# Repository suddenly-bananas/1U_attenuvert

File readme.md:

This module is an attempt to reproduce the functionality of the Intellijel Quadratt for private use (not for sale!), i.e. four independent attenuators/attenuverters, which can be mixed together through normalized mixing, although some modifications are included regarding output LEDs and jack input normalization. The schematics are fairly straightforward and consists mainly of usual inverting opamp mixing stages. Aside from having a new utility module at hand, the main goal of this project was to have a relatively simple module with which I can make my first experiences with SMD-components, SMD-assembly services and 4-layer-PCB-design.

# Picdump

front panel

finished module

assembled PCB and front-panel

layout top

layout bottom

layout power layer

schematics

# Circuit Explanation

The circuit consists of four nearly identical attenuverter cores in the following configuration: 

Each attenuverter core can be switched between attenuator (Gain ranging from 0 to 1) and attenuverter (Gain ranging from -1 to 1) modes. Each input is normalized to +5V or +10V, see the section about input normalization below. If no cable is plugged in the output of its respective channel, the output signal is automatically mixed to the next channel, see the section about output normalization in the documentation.

# [Click here for a detailed analysis of the circuit!](./docu/docu.pdf)

<!-- ## Attenuverter Core Circuit

### Inverting OPamp stages

The core circuit for each channel consists of two unity gain inverting amplifier stages, i.e. stages with a gain of -1. Quick reminder about the golden rules for opamps with negative feedback: Rule 1 states that the opamp will make it so that its two input nodes have the same potential. Rule 2 states that no current can flow into the opamp. With this in mind, the inverting amplifier works as follows:

With this we arrive at:

For having not only a fixed gain of -1 but make it adjustable, one can insert a potentiometer as follows:

In this case, the potentiometer is of course nothing else than two resistors $R_1, R_2$ with $R_{pot} = R_1+R_2$, where $R_{pot}$ is the total resistance of the pot:

As before, by using the opamp rules, this can be analyzed to arrive at a general more general formula for the gain of the circuit. First note, that because of "virtual ground" at the negative terminal of the opamp, $R_1$ and $R_2$ form a current divider as follows:

Solving for $I_1,$ we obtain
$$ I_1 = I - I_2 = I - \frac{R_1}{R_2}\cdot I_1, $$
hence
$$ I = I_1+\frac{R_1}{R_2}\cdot I_1 = (1+\frac{R_1}{R_2})\cdot I_1 $$
and thus 
$$ I_1 = \frac{I}{1+ \frac{R_1}{R_2}}. $$
Writing $R_1||R_2$ for the resistance of $R_1$ parallel to $R_2,$ the total current $I$ is given by
$$ I = \frac{U_{in}}{R_{in} + (R_1||R_2)} = \frac{U_{in}}{R_{in} + \frac{1}{\frac{1}{R_1}+\frac{1}{R_2}}}.$$
This leads to
$$\begin{align*} 
    I_1 &= I\cdot \frac{1}{1+ \frac{R_1}{R_2}} \\
    &= \frac{U_{in}}{R_{in} + \frac{1}{\frac{1}{R_1}+\frac{1}{R_2}}}\cdot \frac{1}{1+ \frac{R_1}{R_2}}\\
    &= \frac{U_{in}}{R_{in} + \frac{R_1R_2}{R_1+R_2}}\cdot \frac{R_2}{R_2+ R_1}\\
    &= \frac{U_{in}R_2}{R_{in}(R_2+R_1) + R_1R_2} \\
    &= \frac{U_{in}R_2}{R_{in}R_{pot} + R_1R_2}
\end{align*}$$
remembering that $R_{pot} = R_2 + R_1$. Again we have $U_{out} = -I_1\cdot R_F$ by inverting opamp amplifier rules and thus arrive at the general formula
$$ U_{out} = -U_{in}\cdot \frac{R_2R_F}{R_{in}R_{pot} + R_1R_2}. $$
Ideally, we would want to have a linear relationship between potentiometer position, i.e. the value of $R_2$, and gain of our circuit. But considering $R_2$ as the parameter of the gain function $f$, i.e.
$$ f(R_2) = - \frac{R_2R_F}{R_{in}R_{pot} + R_1R_2}, $$
this looks all but linear! Luckily, we can make some assumptions, because of course in reality we don't care if it is really mathematically linear or only "linear enough". If we assume for now, that $R_{in}$ is much bigger than $R_{pot},$ then since both $R_1\leq R_{pot}<<R_{in}$ and $R_2\leq R_{pot}<<R_{in},$ we can approximate
$$ R_{in}R_{pot} + R_1R_2 \approx R_{in}R_{pot}. $$
If we further say that $R_{in} = R_F$ (in practice we choose 100k for both), the gain function simplifies to 
$$ f(R_2) \approx \frac{R_2}{R_{pot}}, $$ 
which is linear! Or in other words $U_{out}\approx -U_{in}\cdot \frac{R_2}{R_{pot}}$

So, what value do we choose for $R_{pot}$? The following plots show the gain $-{U_{out}}/{U_{in}}$ of the circuit for different values of $R_{pot}$ and we can easily see that a value of 10k leads to "linear enough".

We close this section with an inverting mixer configuration. It's basically the same as before, but with multiple input voltages and corresponding resistors (Remember that no current can flow inside of the opamp):

So we see, that the output is just an inverted copy of the sum of the two input voltages, but each input scaled acoordingly by $R_1$ and $R_2$ respectively.

### Attenuator / Attenuverter Circuit

Now we come to the actual attenuverter core. Let's have a look at the attenuverter circuit for channel 1:

If the switch connects to ground as in the picture, the situation is exactly as explained before; The first opamp outputs $-U_{in}\cdot c,$ where $c$ is a value between 0 and 1, depending on the pot position (this is approximately $R_2/R_{pot}$ as in the previous section). The next opamp has a gain of $-1$, so the total output is $U_{out} = c\cdot U_{in}.$ Attenuation achieved!

Now assume the switch is in the other position, i.e. one side of the potentiometer is connected to the negative terminal of the second opamp. Since both sides of the potentiometer are connected to input terminals of opamps, they both sit at "virtual ground" aka 0V. Let's analyze some concrete potentiometer positions:

- Pot fully turned clockwise:

Both ends of the potentiometer sit at 0V, no current flows through the pot, so the first opamp outputs $-U_{in}$ and the second one inverts it again, arriving at $U_{out} = U_{in}.$
- Pot in middle position:

As before, the pot divides the current, so roughly half of the input current flow through either side of the pot. The first opamp then outputs roughly $\approx -0.5\cdot U_{in}$. This again forces a negative to current through the 100k-resistor connecting the first opamp to the second one, which then cancels with the current coming from the lower part of the pot. Total output: 0V 
- Pot fully turned counterclockwise:

Again both ends of the potentiometer sit at 0V, so all input current has to flow to the second opamp, which inverts the signal, so we arrive at $U_{out}=-U_{in}.$

For potentiometer positions in between, we interpolate the total gain of the circuit from -1 to 1, somewhat linearly by the choice of 10k for the pot which is small enough relative to the other resistors. In other words: Attenuvertion achieved!

## LED Driver Circuit

The LED driver uses an opamp-circuit that acts as a voltage to current converter:

It works as follows: No current can flow into the opamp, so $I_1 = I_2.$ Furthermore, $U_-=U_+=U_{in},$ so $I_1 = I_2 = U_-/R_2 = U_{in}/R_2.$ Hence the current through $R_1$ is completely determined by the input voltage scaled by the fixed value of $R_2.$ In particular, it depends linearly on $U_{in}!$ Note that the value of $R_1$ is completely irrelevant for this calculation. (At least in theory; in practice, the opamp must be able to supply an output voltage big enough so that $U_- = U_+.$ This works as long as the opamp is not in saturation territory.) Thus, we can easily swap $R_1$ with an LED:

And as such, we have an LED driver where the current through the LED depends linearly on $U_{in}$ and is scaled by the fixed series resistor $R_2.$ Note however, that this works only for positive input voltages, because for a negative input voltage, also $I_2$ and thus $I_1$ would be negative, but this is prevented by orientation of the LED.

In our circuit, we have two LEDs: A yellow one for positive voltages, and a blue one for negative voltages:

While in theory, one could use on opamp for both LEDs by wiring the LEDs in an antiparallel way in the negative feedback loop, our approach has the upside that the series resistor can be chosen individually for each LED. With the LEDs I have (Standard 3mm LEDs from [banzaimusic.com](banzaimusic.com)), if I use the same series resistor for both LEDs, either the yellow one is barely visible or the blue one kills my eyesight. Through testing on breadboard, I arrived at 470 Ohms for the yellow LED and 47 kOhms for the blue LED.

One last note: When using opamps in such a way that the terminals do not sit at 0V, i.e. (virtual) ground, there is an effect called [phase reversal](https://northcoastsynthesis.com/news/whats-the-deal-with-phase-reversal/). In order to prevent this, we scale the voltage goging to the LED drivers by 1/2, using a simple voltage divider. Since the previous stage can output at most +/-12V, this limits the input of the LED-drivers to +/-6V which is a safe range. Of course, this has to be taken into account when choosing appropriate LED series resistors.

## Output Normalization Mixing

As in the Intellijel Quadratt, I wanted to implement mixing through normalization, i.e. if no cable is plugged into the output jack of some channel, the output signal shall automatically be mixed to the output of the next stage. "Simple!" I thought, naive as I am. "I just add the output of one channel through a 100k-resistor to the first opamp-stage of the next channel." (At this point, you have to recall the basic mixing circuit at the end of the section about inverting opamp stages.) Let's see what happens.

First assume the switch of the next channel is in attenuation mode:

Let $U_{prev}$ be the signal from the previous channel and $V_{in}$ be the input signal of the next channel, which is seen by the first opamp after scaling it with the potentiometer. If the sum of both signals $V_{in}+U_{prev}$ is inside the range of +/-12V, everything works as expected as the first opamp stage outputs $-(V_{in}+U_{prev}),$ which by the second opamp stage gets inverted again to arrive at $V_{in}+U_{prev}$ on the output.

If $V_{in}+U_{prev}$ exceeds the range of +/-12V, then the first opamp saturates. In this case this is no problem, since the excess current at the input can just flow through the pot to ground. So the voltage is just clamped at +/-12V in this case, which is also how the circuit is expected to work.

Now assume we are in attenuvertion mode:

With the notation as above, if $V_{in}+U_{prev}$ does not exceed +/-12V, everything works as before, the only difference being that the input voltage $U_{in}$ is processed by both opamp stages as explained in the previous section about the attenuverter circuit.

If the first opamp goes into saturation, however, there are some drastic effects. Assume that $U_{prev}=12V,$ so this signal alone is enough to saturate the opamp so that its output sits at -12V. Also assume that the pot is fully clockwise, so it can be regarded as a resistance of 10k from the negative terminal of the first opamp to the negative terminal of the second opamp. The current $I_1$ through $R_1$ can now not flow through $R_F,$ since the first opamp is already in saturation and thus cannot go any lower than -12V, which would be necessary to sink more current. Hence, $I_1$ must flow through the pot directly to the second opamp. Suppose we have $U_{in}=5V,$ hence $I_1=5V/100k\Omega = 50\mu A.$ In theory, we would want to have the sum $U_{in}+U_{prev}=17V,$ which gets clamped to 12V, at the total output. But what actually happens is, that the second opamp sees $-12V/100k + 50\mu A = -70\mu A$ at its negative input, hence it outputs 7V, to have a current of $7V/100k\Omega = 70\mu A$ flowing from its output through the feedback resistor to its negative terminal. So, actually $U_{in}$ got subtracted from $U_{prev},$ totally not wat we aimed for!

To overcome this problem we changed the feedback resistor of the first opamp stage from 100k to 51k, effectively halving the voltage gain of this stage. This prevents the opamp from ever going into saturation mode if both $U_{prev}$ and $U_{in}$ stay inside a +/-12V-range. Then the resistor going from the first opamp to the second one also has to be changed to 51k, which has the effect that the second opamp has a gain of -2 for the voltage coming out of the first opamp, which reverses the gain halving we did before. 

Note that this is of course not necessary for the first channel, as there is normalization mixing in this case. In practice, this approach has the downside that inherent offset voltages as well as noise from the first opamp get amplified by a factor of 2 by the second opamp. But it has to be seen if this is even noticable in practice. -->

# Changes for Next Version

- If Layout has to be changed: Swap all LEDs to the right of their respective output-jack. This should greatly simplify the PCB layout routing.
- Fix positioning of power pinheader

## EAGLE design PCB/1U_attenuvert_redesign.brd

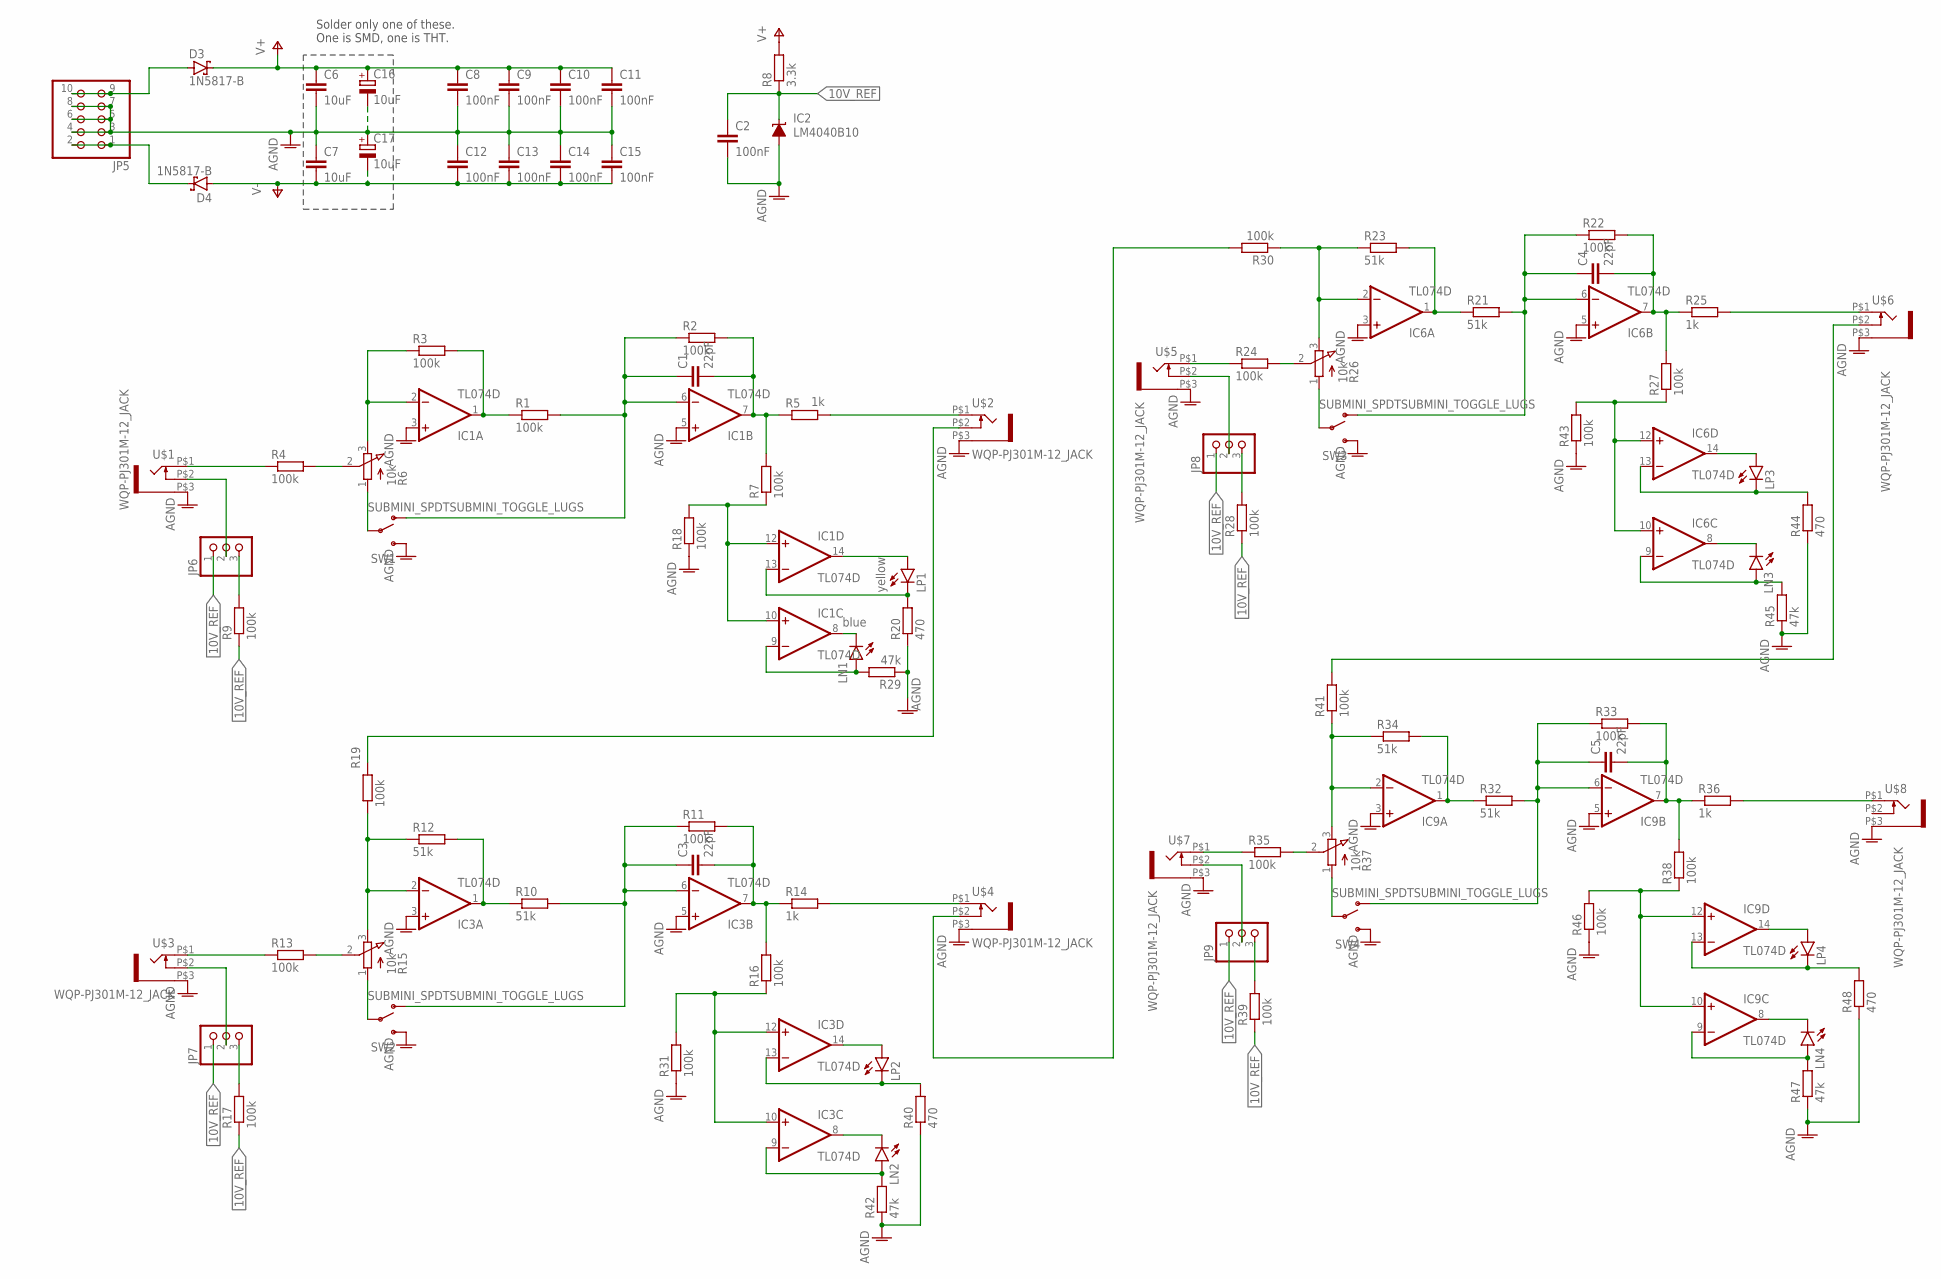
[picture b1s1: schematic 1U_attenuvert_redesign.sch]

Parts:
C1, C3, C4, C5: 22pF; C0603
C2, C8, C9, C10, C11, C12, C13, C14, C15: 100nF; C0603
C6, C7: 10uF; C0805
C16, C17: 10uF; E2,5-6
D3, D4: 1N5817-B; DO41-7.6
IC1, IC3, IC6, IC9: TL074D; SO14
IC2: LM4040B10; DBZ_R-PDSO-G3
JP5: PINHD-2X5; 2X05
JP6, JP7, JP8, JP9: PINHD-1X3; 1X03
LN1: blue; LED3MM
LN2, LN3, LN4: LED3MM
LP1: yellow; LED3MM
LP2, LP3, LP4: LED3MM
R1, R2, R3, R4, R7, R9, R11, R13, R16, R17, R18, R19, R22, R24, R27, R28, R30, R31, R33, R35, R38, R39, R41, R43, R46: 100k; R0603
R5, R14, R25, R36: 1k; R0603
R6, R15, R26, R37: 10k; EVUFXL
R8: 3.3k; R0603
R10, R12, R21, R23, R32, R34: 51k; R0603
R20, R40, R44, R48: 470; R0603
R29, R42, R45, R47: 47k; R0603
SW1, SW2, SW3, SW4: SUBMINI_SPDTSUBMINI_TOGGLE_LUGS; SUBMINI_TOGGLE_LUGS
U$1, U$2, U$3, U$4, U$5, U$6, U$7, U$8: WQP-PJ301M-12_JACK

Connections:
10V_REF: C2.1, IC2.1 (C), JP6.1, JP7.1, JP8.1, JP9.1, R8.1, R9.1, R17.1, R28.1, R39.1
AGND: C2.2, C6.2, C7.1, C8.2, C9.2, C10.2, C11.2, C12.1, C13.1, C14.1, C15.1, C16.-, C17.+, IC1.3 (+IN), IC1.5 (+IN), IC2.2 (A), IC3.3 (+IN), IC3.5 (+IN), IC6.3 (+IN), IC6.5 (+IN), IC9.3 (+IN), IC9.5 (+IN), JP5.3, JP5.4, JP5.5, JP5.6, JP5.7, JP5.8, R18.1, R20.1, R29.1, R31.1, R40.1, R42.1, R43.1, R44.1, R45.1, R46.1, R47.1, R48.1, SW1.3 (S), SW2.3 (S), SW3.3 (S), SW4.3 (S), U$1.P$3 (1), U$2.P$3 (1), U$3.P$3 (1), U$4.P$3 (1), U$5.P$3 (1), U$6.P$3 (1), U$7.P$3 (1), U$8.P$3 (1)
unnamed: C1.1, IC1.6 (-IN), R1.2, R2.1, SW1.1 (O)
unnamed: R4.2, R6.2 (S)
unnamed: IC1.1 (OUT), R1.1, R3.2
unnamed: IC1.2 (-IN), R3.1, R6.3 (E)
unnamed: C1.2, IC1.7 (OUT), R2.2, R5.1, R7.2
unnamed: R5.2, U$2.P$1 (2)
unnamed: R6.1 (A), SW1.COM (COMMON)
unnamed: IC1.10 (+IN), IC1.12 (+IN), R7.1, R18.2
unnamed: R4.1, U$1.P$1 (2)
unnamed: IC1.13 (-IN), LP1.K (C), R20.2
unnamed: JP6.2, U$1.P$2 (3)
unnamed: C3.1, IC3.6 (-IN), R10.2, R11.1, SW2.1 (O)
unnamed: JP6.3, R9.2
unnamed: IC3.1 (OUT), R10.1, R12.2
unnamed: IC3.2 (-IN), R12.1, R15.3 (E), R19.1
unnamed: C3.2, IC3.7 (OUT), R11.2, R14.1, R16.2
unnamed: R14.2, U$4.P$1 (2)
unnamed: R13.2, R15.2 (S)
unnamed: R15.1 (A), SW2.COM (COMMON)
unnamed: IC3.9 (-IN), LN2.A, R42.2
unnamed: IC1.8 (OUT), LN1.K (C)
unnamed: R13.1, U$3.P$1 (2)
unnamed: JP7.2, U$3.P$2 (3)
unnamed: JP7.3, R17.2
unnamed: R19.2, U$2.P$2 (3)
unnamed: IC1.9 (-IN), LN1.A, R29.2
unnamed: IC3.10 (+IN), IC3.12 (+IN), R16.1, R31.2
unnamed: C4.1, IC6.6 (-IN), R21.2, R22.1, SW3.1 (O)
unnamed: IC6.1 (OUT), R21.1, R23.2
unnamed: IC6.2 (-IN), R23.1, R26.3 (E), R30.1
unnamed: C4.2, IC6.7 (OUT), R22.2, R25.1, R27.2
unnamed: R25.2, U$6.P$1 (2)
unnamed: R24.2, R26.2 (S)
unnamed: R26.1 (A), SW3.COM (COMMON)
unnamed: IC6.10 (+IN), IC6.12 (+IN), R27.1, R43.2
unnamed: IC6.8 (OUT), LN3.K (C)
unnamed: R24.1, U$5.P$1 (2)
unnamed: JP8.2, U$5.P$2 (3)
unnamed: JP8.3, R28.2
unnamed: R30.2, U$4.P$2 (3)
unnamed: IC3.13 (-IN), LP2.K (C), R40.2
unnamed: IC6.9 (-IN), LN3.A, R45.2
unnamed: C5.1, IC9.6 (-IN), R32.2, R33.1, SW4.1 (O)
unnamed: IC9.1 (OUT), R32.1, R34.2
unnamed: IC9.2 (-IN), R34.1, R37.3 (E), R41.1
unnamed: C5.2, IC9.7 (OUT), R33.2, R36.1, R38.2
unnamed: R36.2, U$8.P$1 (2)
unnamed: R35.2, R37.2 (S)
unnamed: R37.1 (A), SW4.COM (COMMON)
unnamed: IC9.9 (-IN), LN4.A, R47.2
unnamed: IC9.10 (+IN), IC9.12 (+IN), R38.1, R46.2
unnamed: R35.1, U$7.P$1 (2)
unnamed: JP9.2, U$7.P$2 (3)
unnamed: JP9.3, R39.2
unnamed: R41.2, U$6.P$2 (3)
unnamed: IC1.14 (OUT), LP1.A
unnamed: IC3.8 (OUT), LN2.K (C)
unnamed: IC6.13 (-IN), LP3.K (C), R44.2
unnamed: IC3.14 (OUT), LP2.A
unnamed: IC6.14 (OUT), LP3.A
unnamed: D4.C, JP5.1, JP5.2
unnamed: D3.A, JP5.9, JP5.10
unnamed: IC9.13 (-IN), LP4.K (C), R48.2
unnamed: IC9.14 (OUT), LP4.A
unnamed: IC9.8 (OUT), LN4.K (C)
V+: C6.1, C8.1, C9.1, C10.1, C11.1, C16.+, D3.C, IC1.4 (V+), IC3.4 (V+), IC6.4 (V+), IC9.4 (V+), R8.2
V-: C7.2, C12.2, C13.2, C14.2, C15.2, C17.-, D4.A, IC1.11 (V-), IC3.11 (V-), IC6.11 (V-), IC9.11 (V-)

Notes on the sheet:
Solder only one of these. One is SMD, one is THT.

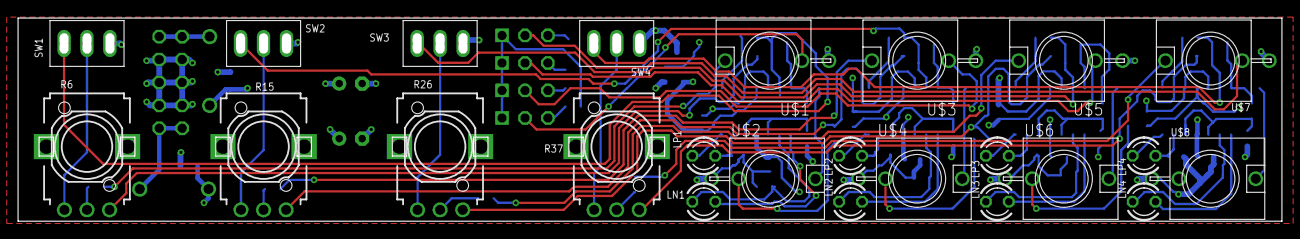
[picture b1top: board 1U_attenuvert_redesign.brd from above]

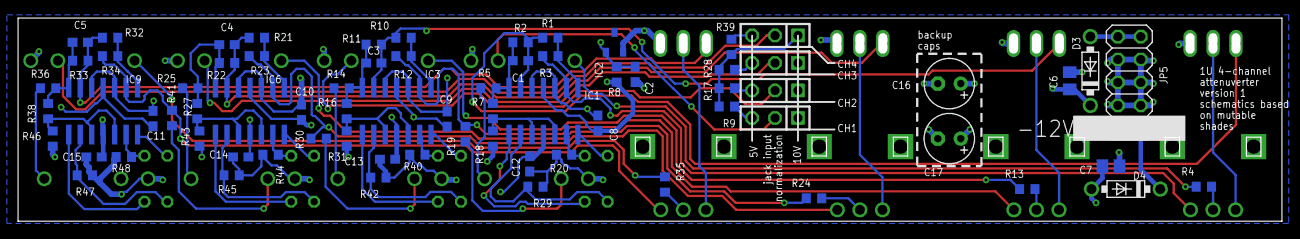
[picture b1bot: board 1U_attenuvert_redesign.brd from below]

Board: 4 copper layers, 139.0 x 21.5 mm, 97 parts (73 on the bottom side), 69 nets.

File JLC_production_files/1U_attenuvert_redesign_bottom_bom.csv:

Comment,Designator,Footprint,LCSC Part #
1k,R5 R14 R25 R36,R0603,
3.3k,R8,R0603,
10uF,C6 C7,C0805,
22pF,C1 C3 C4 C5,C0603,
47k,R29 R42 R45 R47,R0603,
51k,R10 R12 R21 R23 R32 R34,R0603,
100k,R1 R2 R3 R4 R7 R9 R11 R13 R16 R17 R18 R19 R22 R24 R27 R28 R30 R31 R33 R35 R38 R39 R41 R43 R46,R0603,
100nF,C2 C8 C9 C10 C11 C12 C13 C14 C15,C0603,
470,R20 R40 R44 R48,R0603,
LM4040B10,IC2,DBZ_R-PDSO-G3,
TL074D,IC1 IC3 IC6 IC9,SO14,

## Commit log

2026-02-16 fixed docu link in readme
2026-02-16 updated docu
2026-05-13 added photos
